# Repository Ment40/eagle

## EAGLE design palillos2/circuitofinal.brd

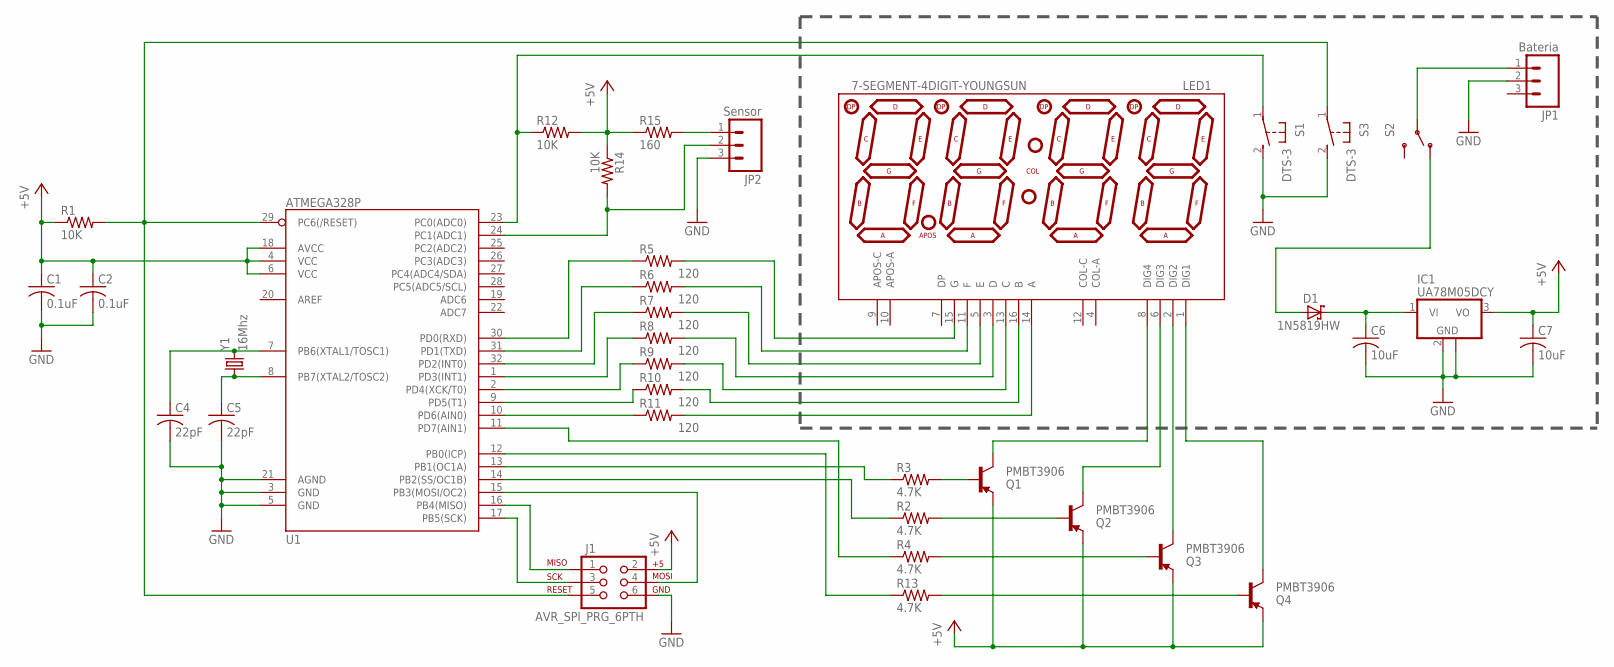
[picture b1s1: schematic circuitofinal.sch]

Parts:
C1, C2: 0.1uF; C0805
C4, C5: 22pF; C1206
C6, C7: 10uF; C1206
D1: 1N5819HW; SOD-123
IC1: UA78M05DCY; SOT223
J1: AVR_SPI_PRG_6PTH; 2X3
JP1: Bateria; JST-3-PTH
JP2: Sensor; JST-3-PTH
LED1: 7-SEGMENT-4DIGIT-YOUNGSUN
Q1, Q2, Q3, Q4: PMBT3906; SOT23-3
R1, R12, R14: 10K; R0805
R2, R3, R4, R13: 4.7K; R0805
R5, R6, R7, R8, R9, R10, R11: 120; R0805
R15: 160; R1206
S1, S3: DTS-3
S2: SWITCH-SPDTPTH; SWITCH-SPDT
U1: ATMEGA328P; TQFP32-08
Y1: 16Mhz; HC49US

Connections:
+5V: C1.1, C2.1, C7.1, IC1.3 (VO), J1.2, Q1.2 (E), Q2.2 (E), Q3.2 (E), Q4.2 (E), R1.1, R12.2, R14.1, R15.1, U1.4 (VCC), U1.6 (VCC), U1.18 (AVCC)
GND: C1.2, C2.2, C4.2, C5.2, C6.2, C7.2, IC1.2 (GND), IC1.4 (GND), J1.6, JP1.2, JP2.3, S1.2, S3.2, U1.3 (GND), U1.5 (GND), U1.21 (AGND)
unnamed: Q2.1 (B), R2.2
unnamed: Q3.1 (B), R4.2
unnamed: Q4.1 (B), R13.2
unnamed: LED1.8 (DIG4), Q1.3 (C)
unnamed: LED1.3 (D), R8.2
unnamed: LED1.6 (DIG3), Q2.3 (C)
unnamed: LED1.16 (B), R10.2
unnamed: LED1.14 (A), R11.2
unnamed: JP1.1, S2.2
unnamed: C6.1, D1.C, IC1.1 (VI)
unnamed: LED1.11 (F), R6.2
unnamed: R12.1, S1.1, U1.23 (PC0(ADC0))
unnamed: Q1.1 (B), R3.2
unnamed: C4.1, U1.7 (PB6(XTAL1/TOSC1)), Y1.2
unnamed: C5.1, U1.8 (PB7(XTAL2/TOSC2)), Y1.1
unnamed: JP2.2, R14.2, U1.24 (PC1(ADC1))
unnamed: J1.3, U1.17 (PB5(SCK))
unnamed: J1.1, U1.16 (PB4(MISO))
unnamed: J1.4, U1.15 (PB3(MOSI/OC2))
unnamed: LED1.1 (DIG1), Q4.3 (C)
unnamed: LED1.2 (DIG2), Q3.3 (C)
unnamed: R3.1, U1.13 (PB1(OC1A))
unnamed: R2.1, U1.14 (PB2(SS/OC1B))
unnamed: R4.1, U1.11 (PD7(AIN1))
unnamed: R5.1, U1.30 (PD0(RXD))
unnamed: R6.1, U1.31 (PD1(TXD))
unnamed: R7.1, U1.32 (PD2(INT0))
unnamed: R10.1, U1.9 (PD5(T1))
unnamed: R11.1, U1.10 (PD6(AIN0))
unnamed: LED1.15 (G), R5.2
unnamed: R13.1, U1.12 (PB0(ICP))
unnamed: D1.A, S2.1 (O)
unnamed: LED1.5 (E), R7.2
unnamed: JP2.1, R15.2
unnamed: J1.5, R1.2, S3.1, U1.29 (PC6(/RESET))
unnamed: LED1.13 (C), R9.2
PIN1: R8.1, U1.1 (PD3(INT1))
PIN2: R9.1, U1.2 (PD4(XCK/T0))

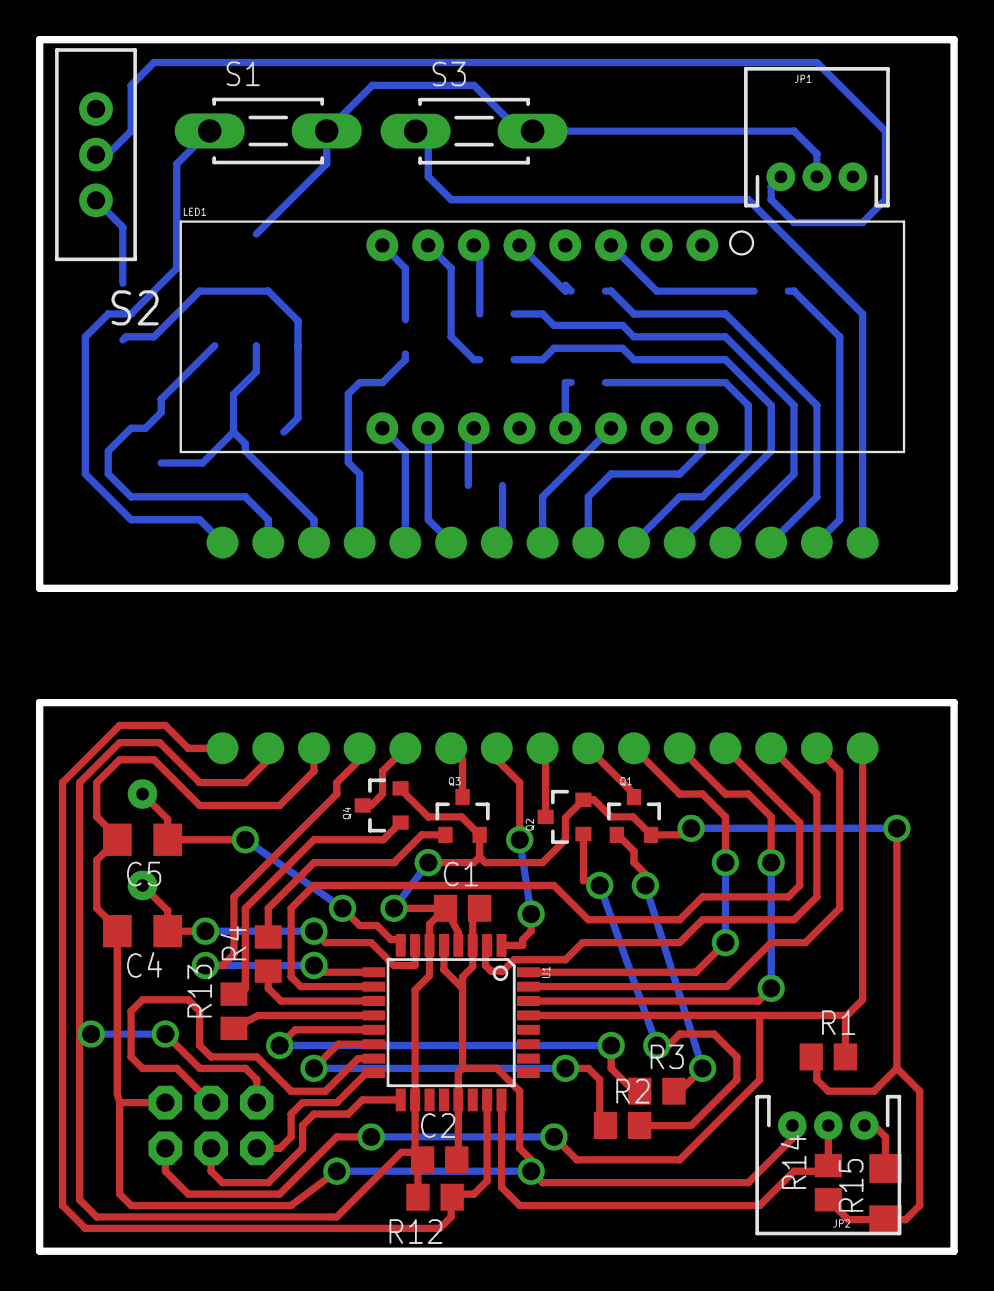
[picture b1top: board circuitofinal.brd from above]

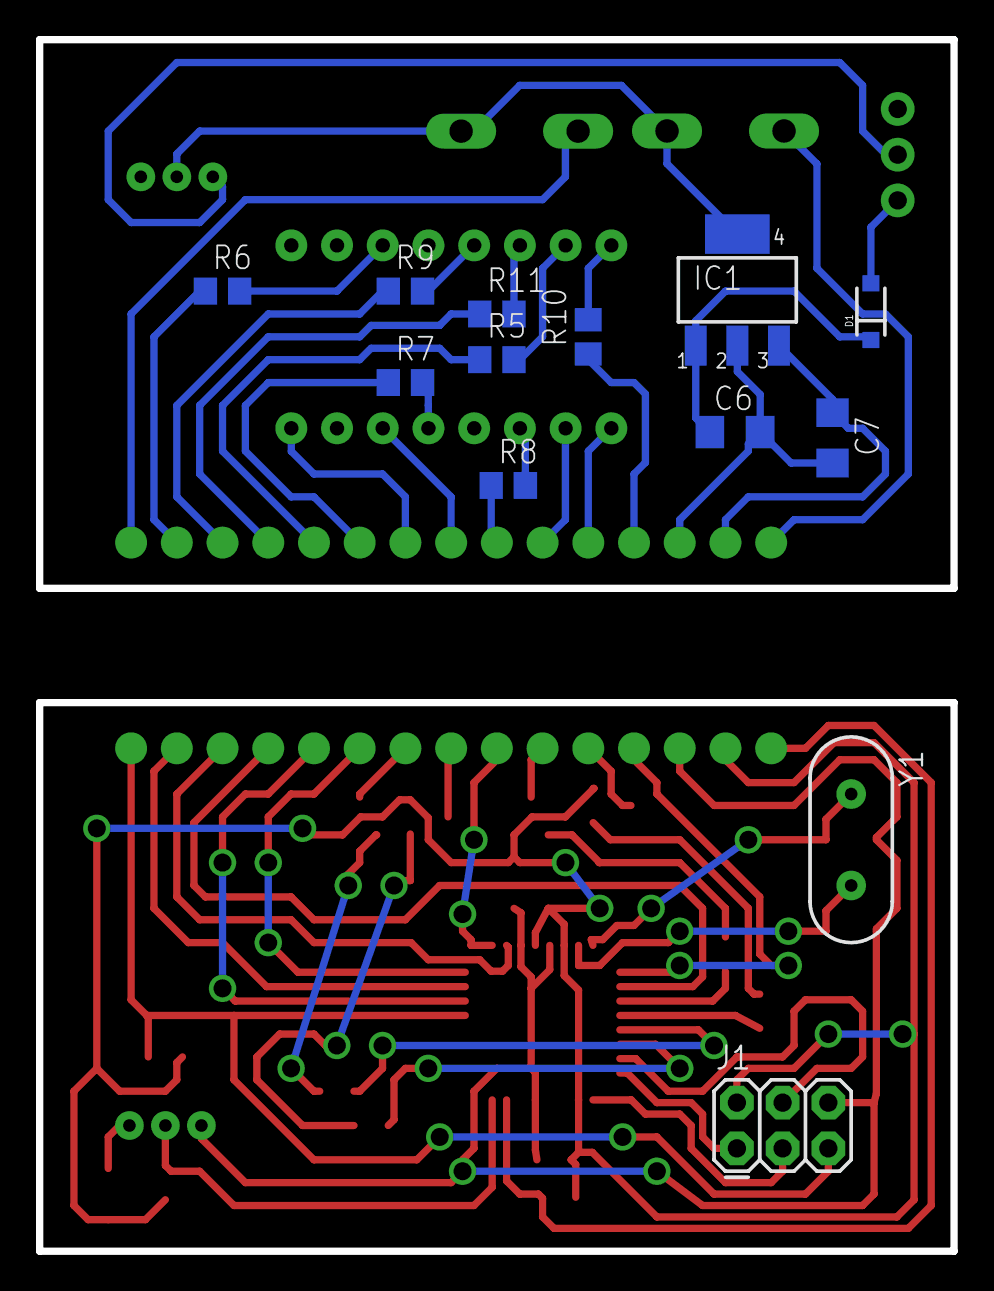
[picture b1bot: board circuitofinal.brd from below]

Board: 2 copper layers, 50.8 x 67.3 mm, 36 parts (13 on the bottom side), 40 nets.

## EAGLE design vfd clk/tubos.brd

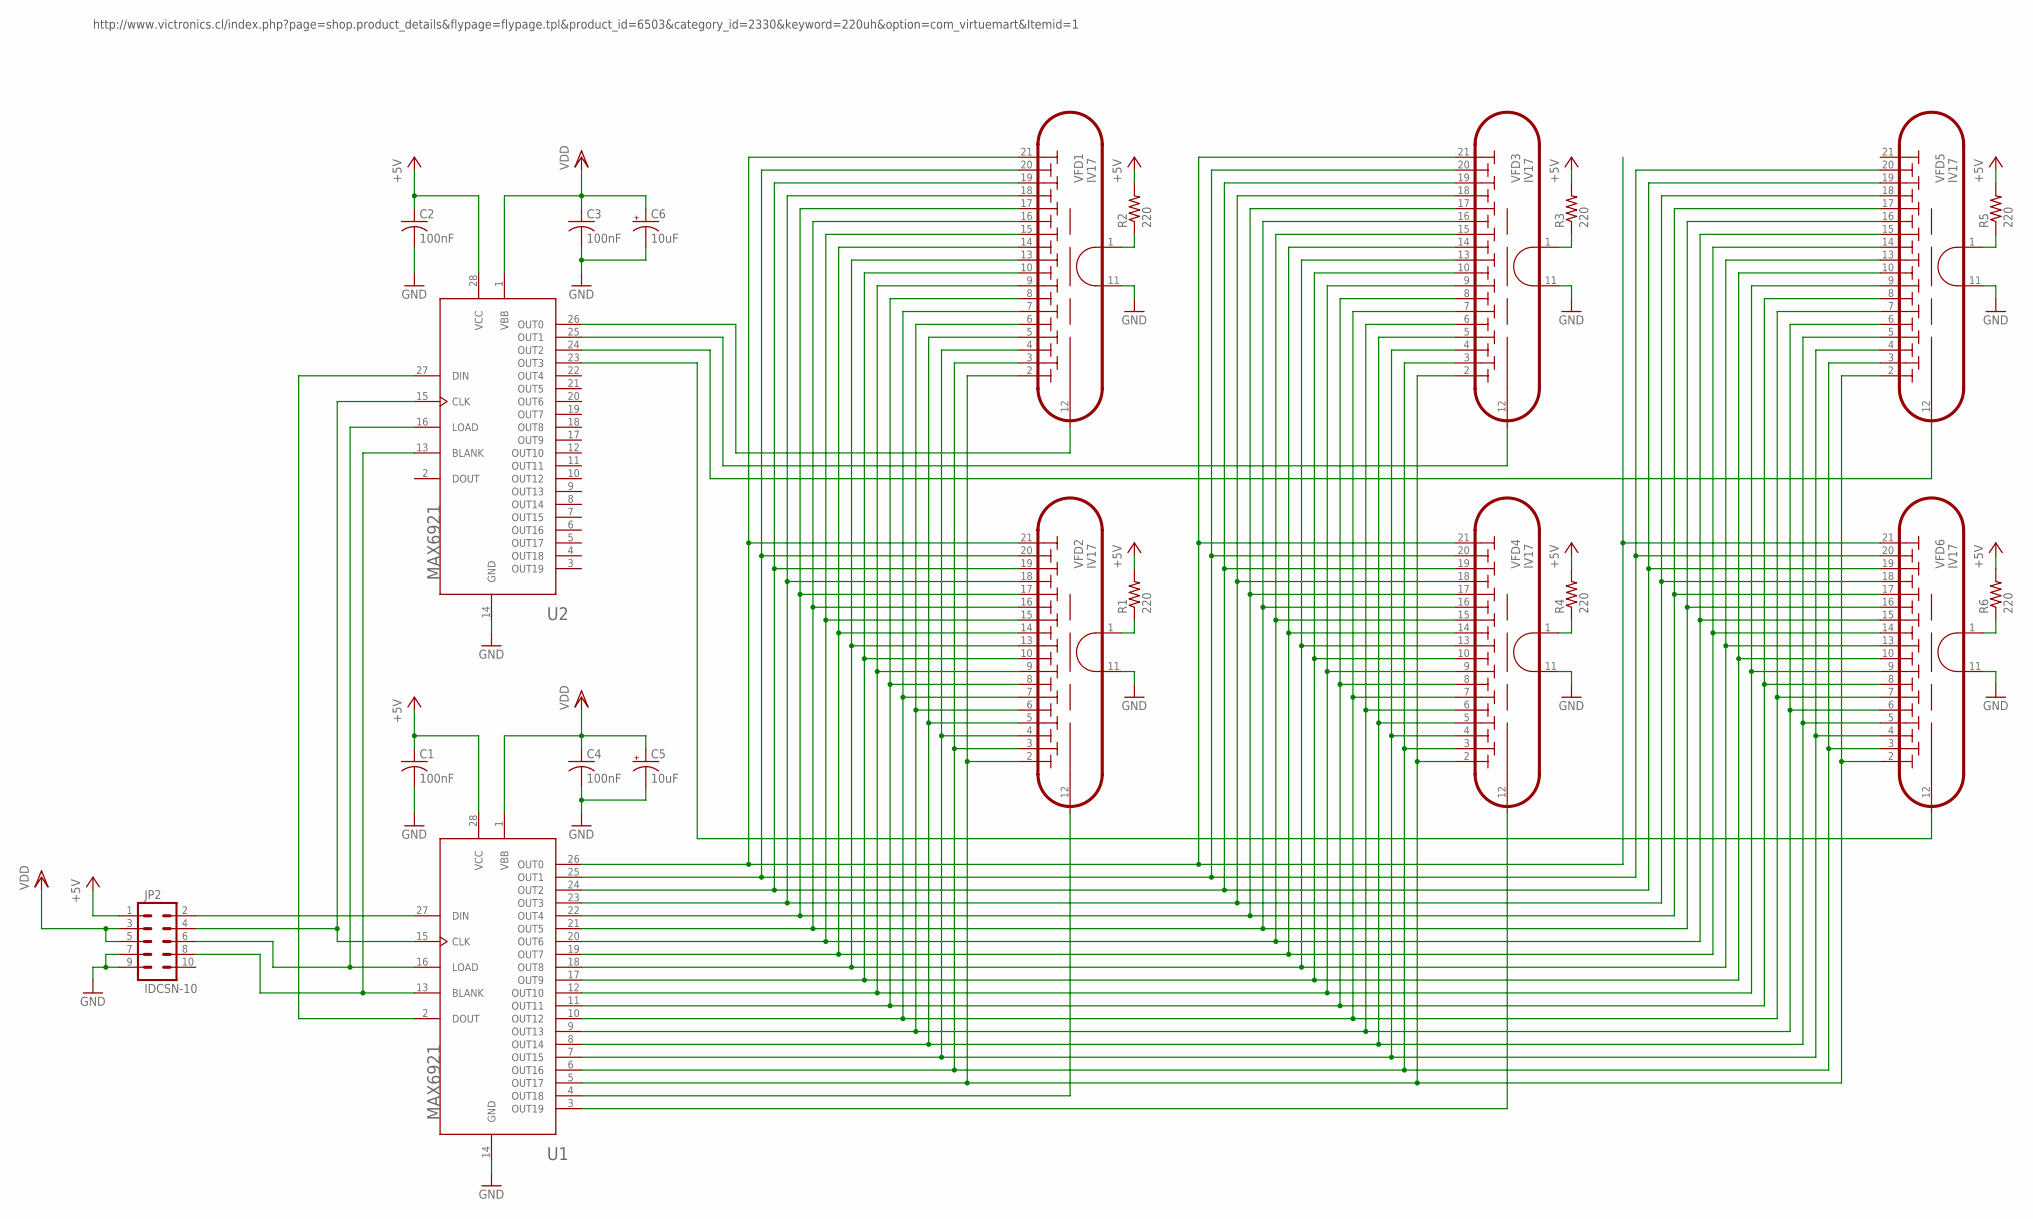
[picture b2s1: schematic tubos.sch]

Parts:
C1, C2: 100nF; C1206
C3, C4: 100nF; C1210
C5, C6: NACEW100M100V6.3X8TR
JP2: IDCSN-10
R1, R2, R3, R4, R5, R6: 220; AXIAL-0.4
U1, U2: MAX6921AWI; SO28W
VFD1, VFD2, VFD3, VFD4, VFD5, VFD6: IV17; CIRCULAR

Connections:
+5V: C1.1, C2.1, JP2.1, R1.P$2 (2), R2.P$2 (2), R3.P$2 (2), R4.P$2 (2), R5.P$2 (2), R6.P$2 (2), U1.28 (VCC), U2.28 (VCC)
GND: C1.2, C2.2, C3.2, C4.2, C5.NEG (-), C6.NEG (-), JP2.7, JP2.9, U1.14 (GND), U2.14 (GND), VFD1.11, VFD2.11, VFD3.11, VFD4.11, VFD5.11, VFD6.11
unnamed: U1.5 (OUT17), VFD1.2, VFD2.2, VFD3.2, VFD4.2, VFD5.2, VFD6.2
unnamed: R2.P$1 (1), VFD1.1
unnamed: U1.7 (OUT15), VFD1.4, VFD2.4, VFD3.4, VFD4.4, VFD5.4, VFD6.4
unnamed: R1.P$1 (1), VFD2.1
unnamed: U1.9 (OUT13), VFD1.6, VFD2.6, VFD3.6, VFD4.6, VFD5.6, VFD6.6
unnamed: R3.P$1 (1), VFD3.1
unnamed: U1.11 (OUT11), VFD1.8, VFD2.8, VFD3.8, VFD4.8, VFD5.8, VFD6.8
unnamed: U1.12 (OUT10), VFD1.9, VFD2.9, VFD3.9, VFD4.9, VFD5.9, VFD6.9
unnamed: R6.P$1 (1), VFD6.1
unnamed: U1.18 (OUT8), VFD1.13, VFD2.13, VFD3.13, VFD4.13, VFD5.13, VFD6.13
unnamed: R5.P$1 (1), VFD5.1
unnamed: U1.20 (OUT6), VFD1.15, VFD2.15, VFD3.15, VFD4.15, VFD5.15, VFD6.15
unnamed: U1.21 (OUT5), VFD1.16, VFD2.16, VFD3.16, VFD4.16, VFD5.16, VFD6.16
unnamed: U1.22 (OUT4), VFD1.17, VFD2.17, VFD3.17, VFD4.17, VFD5.17, VFD6.17
unnamed: R4.P$1 (1), VFD4.1
unnamed: U1.24 (OUT2), VFD1.19, VFD2.19, VFD3.19, VFD4.19, VFD5.19, VFD6.19
unnamed: U1.25 (OUT1), VFD1.20, VFD2.20, VFD3.20, VFD4.20, VFD5.20, VFD6.20
unnamed: U1.4 (OUT18), VFD2.12
unnamed: U1.3 (OUT19), VFD4.12
unnamed: U1.6 (OUT16), VFD1.3, VFD2.3, VFD3.3, VFD4.3, VFD5.3, VFD6.3
unnamed: U2.26 (OUT0), VFD1.12
unnamed: U1.8 (OUT14), VFD1.5, VFD2.5, VFD3.5, VFD4.5, VFD5.5, VFD6.5
unnamed: U2.25 (OUT1), VFD3.12
unnamed: U1.10 (OUT12), VFD1.7, VFD2.7, VFD3.7, VFD4.7, VFD5.7, VFD6.7
unnamed: U2.24 (OUT2), VFD5.12
unnamed: U2.23 (OUT3), VFD6.12
unnamed: U1.17 (OUT9), VFD1.10, VFD2.10, VFD3.10, VFD4.10, VFD5.10, VFD6.10
unnamed: U1.2 (DOUT), U2.27 (DIN)
unnamed: U1.19 (OUT7), VFD1.14, VFD2.14, VFD3.14, VFD4.14, VFD5.14, VFD6.14
unnamed: JP2.4, U1.15 (CLK), U2.15 (CLK)
unnamed: JP2.6, U1.16 (LOAD), U2.16 (LOAD)
unnamed: JP2.8, U1.13 (BLANK), U2.13 (BLANK)
unnamed: U1.23 (OUT3), VFD1.18, VFD2.18, VFD3.18, VFD4.18, VFD5.18, VFD6.18
unnamed: JP2.2, U1.27 (DIN)
unnamed: U1.26 (OUT0), VFD1.21, VFD2.21, VFD3.21, VFD4.21, VFD6.21
VDD: C3.1, C4.1, C5.POS (+), C6.POS (+), JP2.3, JP2.5, U1.1 (VBB), U2.1 (VBB)

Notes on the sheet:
http://www.victronics.cl/index.php?page=shop.product_details&flypage=flypage.tpl&product_id=6503&category_id=2330&keyword=220uh&option=com_virtuemart&Itemid=1

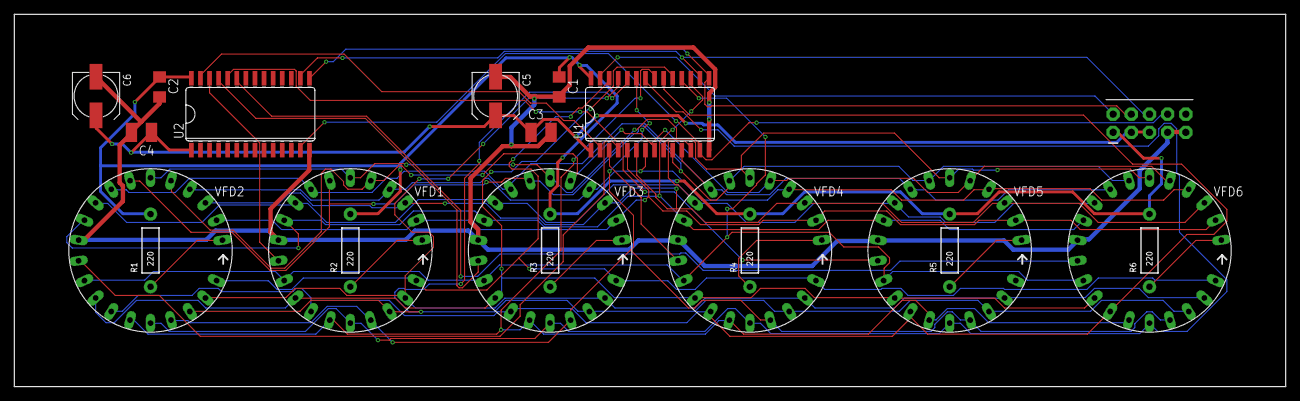
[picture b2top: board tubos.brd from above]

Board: 2 copper layers, 177.8 x 52.1 mm, 21 parts (0 on the bottom side), 38 nets.

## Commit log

2014-12-16 :boom::camel: Added .gitattributes & .gitignore files
2014-12-16 primera subida

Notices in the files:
parts and their libraries:
SparkFun-Connectors: Licensing: Creative Commons ShareAlike 4.0 International - https://creativecommons.org/licenses/by-sa/4.0
